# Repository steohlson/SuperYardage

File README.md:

# SuperYardage
Bradley SAE RC Car

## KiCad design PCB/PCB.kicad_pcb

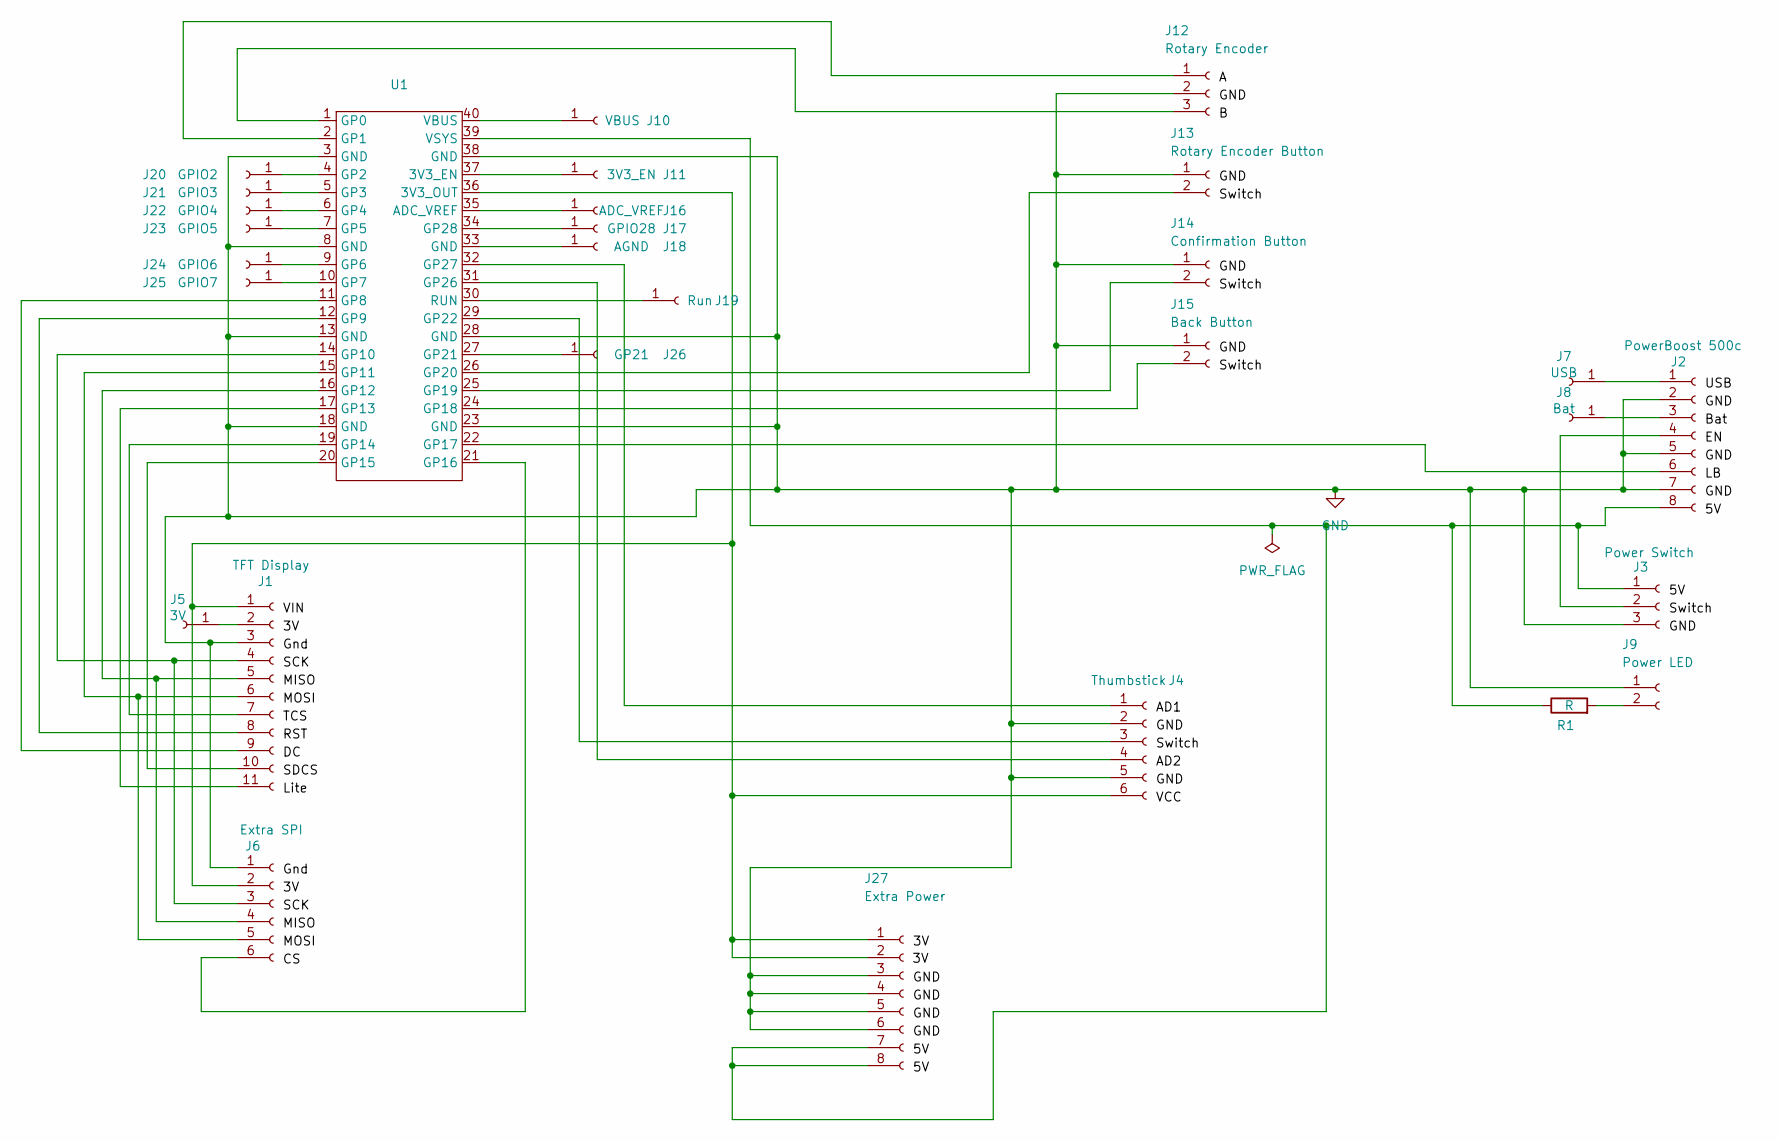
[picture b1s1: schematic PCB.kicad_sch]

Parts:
J1: TFT Display; PinHeader_1x11_P2.54mm_Vertical
J2: PowerBoost 500c; PinHeader_1x08_P2.54mm_Vertical
J3: Power Switch; PinHeader_1x03_P2.54mm_Vertical
J4: Thumbstick; PinHeader_1x06_P2.54mm_Vertical
J5: 3V; PinHeader_1x01_P2.54mm_Vertical
J6: Extra SPI; PinHeader_1x06_P2.54mm_Vertical
J7: USB; PinHeader_1x01_P2.54mm_Vertical
J8: Bat; PinHeader_1x01_P2.54mm_Vertical
J9: Power LED; PinHeader_1x02_P2.54mm_Vertical
J10: VBUS; PinHeader_1x01_P2.54mm_Vertical
J11: 3V3_EN; PinHeader_1x01_P2.54mm_Vertical
J12: Rotary Encoder; PinHeader_1x03_P2.54mm_Vertical
J13: Rotary Encoder Button; PinHeader_1x02_P2.54mm_Vertical
J14: Confirmation Button; PinHeader_1x02_P2.54mm_Vertical
J15: Back Button; PinHeader_1x02_P2.54mm_Vertical
J16: ADC_VREF; PinHeader_1x01_P2.54mm_Vertical
J17: GPIO28; PinHeader_1x01_P2.54mm_Vertical
J18: AGND; PinHeader_1x01_P2.54mm_Vertical
J19: Run; PinHeader_1x01_P2.54mm_Vertical
J20: GPIO2; PinHeader_1x01_P2.54mm_Vertical
J21: GPIO3; PinHeader_1x01_P2.54mm_Vertical
J22: GPIO4; PinHeader_1x01_P2.54mm_Vertical
J23: GPIO5; PinHeader_1x01_P2.54mm_Vertical
J24: GPIO6; PinHeader_1x01_P2.54mm_Vertical
J25: GPIO7; PinHeader_1x01_P2.54mm_Vertical
J26: GP21; PinHeader_1x01_P2.54mm_Vertical
J27: Extra Power; PinHeader_1x08_P2.54mm_Vertical
R1: R; R_Axial_DIN0204_L3.6mm_D1.6mm_P5.08mm_Horizontal
U1: RasPi_Pico

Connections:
GND: J1.3, J2.2, J2.5, J2.7, J3.3, J4.2, J4.5, J6.1, J9.1, J12.2, J13.1, J14.1, J15.1, J27.3, J27.4, J27.5, J27.6, U1.3 (GND), U1.8 (GND), U1.13 (GND), U1.18 (GND), U1.23 (GND), U1.28 (GND), U1.38 (GND)
unnamed: J1.1, J4.6, J6.2, J27.1, J27.2, U1.36 (3V3_OUT)
unnamed: J1.2, J5.1
unnamed: J1.4, J6.3, U1.14 (GP10)
unnamed: J1.5, J6.4, U1.16 (GP12)
unnamed: J1.6, J6.5, U1.15 (GP11)
unnamed: J1.7, U1.19 (GP14)
unnamed: J1.8, U1.12 (GP9)
unnamed: J1.9, U1.11 (GP8)
unnamed: J1.10, U1.20 (GP15)
unnamed: J1.11, U1.17 (GP13)
unnamed: J2.1, J7.1
unnamed: J2.3, J8.1
unnamed: J2.4, J3.2
unnamed: J2.6, U1.22 (GP17)
unnamed: J2.8, J3.1, J27.7, J27.8, R1.1, U1.39 (VSYS)
unnamed: J4.1, U1.32 (GP27)
unnamed: J4.3, U1.29 (GP22)
unnamed: J4.4, U1.31 (GP26)
unnamed: J6.6, U1.21 (GP16)
unnamed: J9.2, R1.2
unnamed: J10.1, U1.40 (VBUS)
unnamed: J11.1, U1.37 (3V3_EN)
unnamed: J12.1, U1.2 (GP1)
unnamed: J12.3, U1.1 (GP0)
unnamed: J13.2, U1.26 (GP20)
unnamed: J14.2, U1.25 (GP19)
unnamed: J15.2, U1.24 (GP18)
unnamed: J16.1, U1.35 (ADC_VREF)
unnamed: J17.1, U1.34 (GP28)
unnamed: J18.1, U1.33 (GND)
unnamed: J19.1, U1.30 (RUN)
unnamed: J20.1, U1.4 (GP2)
unnamed: J21.1, U1.5 (GP3)
unnamed: J22.1, U1.6 (GP4)
unnamed: J23.1, U1.7 (GP5)
unnamed: J24.1, U1.9 (GP6)
unnamed: J25.1, U1.10 (GP7)
unnamed: J26.1, U1.27 (GP21)

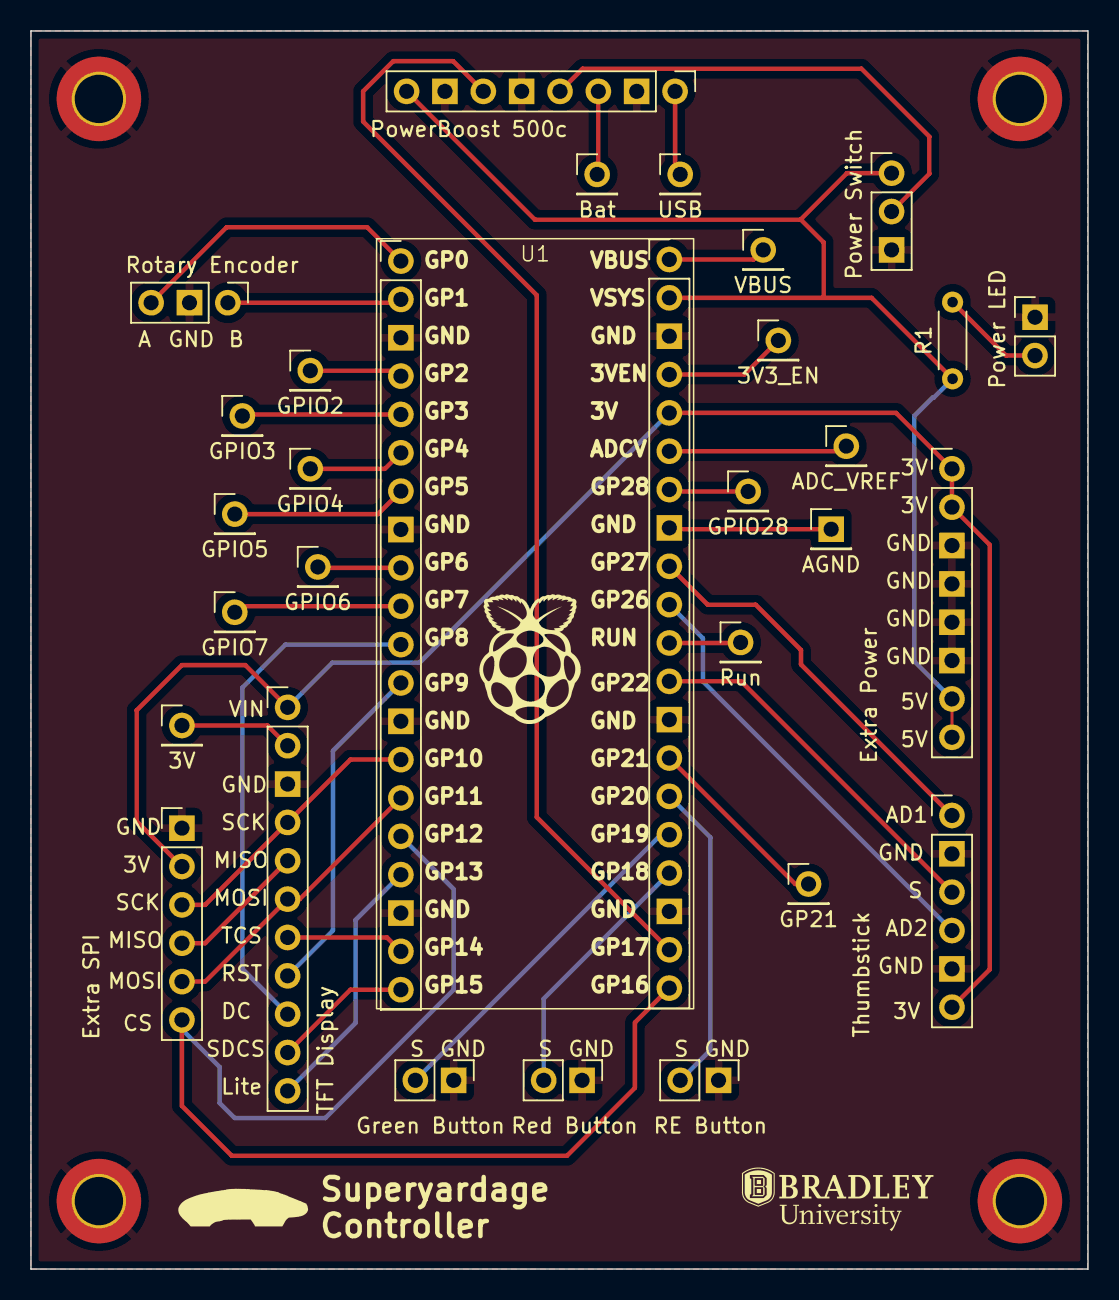
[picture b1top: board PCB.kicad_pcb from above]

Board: 2 copper layers, 70.0 x 82.0 mm, 29 parts (0 on the bottom side), 39 nets.

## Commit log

2024-06-07 Added Parts List
2024-06-16 Micropython setup, code not functional yet
2024-06-16 Code to run 170x320 TFT display with Rasp Pi Pico. Simply displays image
2024-06-26 Code for displaying cpu temp to tft display, pcb changes
2024-06-29 Modularizing code
2024-07-07 Added joystick functionality to InputManager
2024-07-07 Added more display functionality
2024-07-09 Finished controller schematic and mostly finished pcb
2024-07-13 Finished PCB, Last commit before moving to Bradley Org
